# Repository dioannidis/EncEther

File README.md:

# EncEther

( version 3 )

   A single side, through hole, Arduino ethernet shield, designed in Kicad 5. 

### Main IC's

   * ENC28J60        10Base-T stand-alone ethernet controller
   * SN74HCT125N     3 state quadruple buffer for level shifting

   ( all the components datasheets can be found in the DATASHEETS directory )

### Board Info / Tips

   * As a single side board jumper wires are hard to avoid. Currently, exists 16 jumper wires, which are to be soldered first.
   * The L1 4μH inductor, is for EMC ( as per datasheet ), so you can replace it with a jumper wire.
   * The R3, R4, R11 and R12 are 49.9 Ω 1% 1/4W resistors ( as per datasheet ) but I'm using 51 Ω 1% 1/4W with success. The 49.9 Ω 1% ones are hard to find ( at least I can't find them easily ).
   * Because some jumper wires are routed under the sockets, use precision sockets which have more room under them.
   * The MagJack I use is the LMJTAB881243ML from AMPHENOL. You can find it at [TME](https://www.tme.eu/en/details/lmjtab881243m-l/rj-connectors/amphenol/lmjtab881243ml) or at [Grobotronics](https://grobotronics.com/rj45-ethernet-magjack-compatible.html) ( cheaper ).
   * The wakeup and clkout pins of ENC28J60 are not exposed. As this is an UNO shield, there is no need to provide clock to the MCU, it has it's own. And AFAIK, UIPEthernet doesn't implement the wakeup function.

### Board Configuration 

   * Jumper J3

      The CS/SS ( chip select / slave select ) signal can be connected to Arduino Pin 10 or Pin 9 using the J3 jumper.

         * Jumper on the 1-2 pins connects CS/SS to Arduino Pin 10. ( default )
         * Jumper on the 2-3 pins connects CS/SS to Arduino Pin 9.

      The Interrupt pin from the ENC28J60 it can be connected to Arduino Pin 9 or Pin 8 using the J3 jumper.

         * Jumper on the 3-4 pins connects the ENC28J60's interrupt pin to Arduino Pin 9.
         * Jumper on the 4-5 pins connects the ENC28J60's interrupt pin to Arduino Pin 8.

      Optionally, you can populate the U4 socket with an AT24MAC402-602 on a 8-Pin SOIC to DIP adapter ( something like [this](https://www.sparkfun.com/products/13655) or [this](https://www.adafruit.com/product/1212) ) to have a legit MAC Address and an extra 2Kbit serial EEPROM.

   * Jumper J4

      The I2C address of the AT24MAC402-602 can be selected using Jumper J3 as :
		
         * Jumper on 2-3 pins address is 0. ( default )
         * Jumper on 1-2 pins address is 1.

### Examples

( in EXAMPLES directory. Of course the examples work with any ENC28J60 board / module. )

   * EthernetRest 
	  
      Uses the  and  libraries.
	   
      Using the  you can control all digital and analog pins and / or executing custom functions or read custom variables.

### Gallery

   Those pictures are from v1. It didn't have the AT24MAC402-602 option and the CS/SS Pin selection designed yet.

   As you can see in the picture below, the AT24MAC402, is on the small red 8-Pin SOIC to DIP adapter on the breadboard.

-----

Copyright © 2020 Dimitrios Chr. Ioannidis

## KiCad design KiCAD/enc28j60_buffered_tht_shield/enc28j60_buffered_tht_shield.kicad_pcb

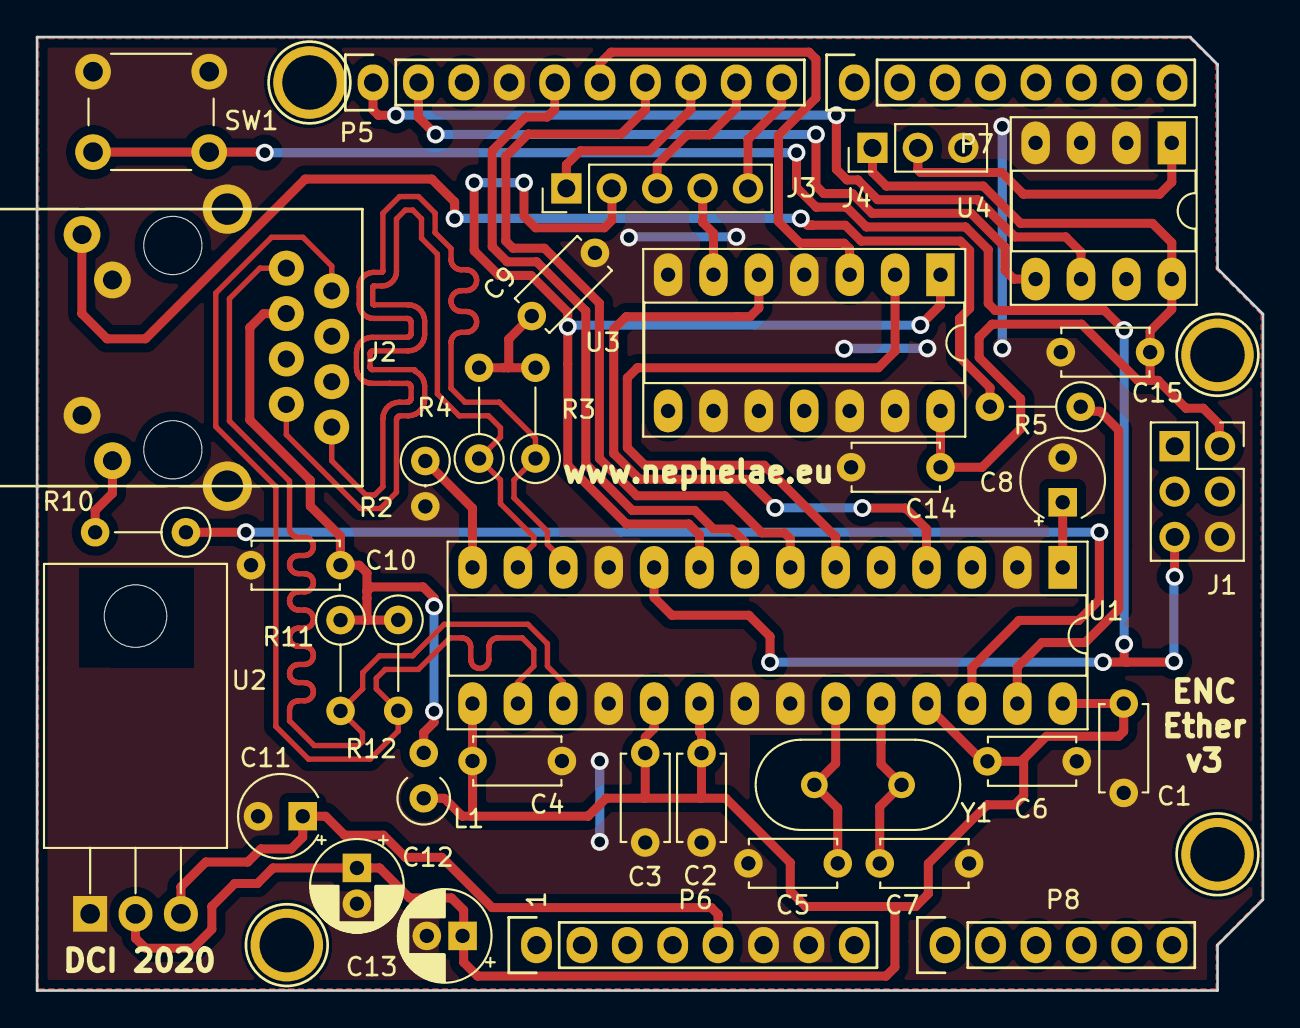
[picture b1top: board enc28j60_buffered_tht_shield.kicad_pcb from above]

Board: 2 copper layers, 68.6 x 53.3 mm, 41 parts (0 on the bottom side), 32 nets.

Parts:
C1, C2, C3, C4, C6, C9, C10, C14, C15: 100 nF; C_Disc_D4.7mm_W2.5mm_P5.00mm
C5, C7: 18 pF; C_Disc_D4.7mm_W2.5mm_P5.00mm
C8, C11: 10 μF ( Low ESR ); CP_Radial_Tantal_D4.5mm_P2.50mm
C12: 10 μF; CP_Radial_D5.0mm_P2.00mm
C13: 100 μF; CP_Radial_D5.0mm_P2.00mm
J1: AVR-ISP-6; PinSocket_2x03_P2.54mm_Vertical
J2: RJ45_MagJack_LMJTAB881X43M-L
J3: Conn_01x05_Male; PinHeader_1x05_P2.54mm_Vertical
J4: Conn_01x03_Male; PinHeader_1x03_P2.54mm_Vertical
L1: 4 μH; L_Axial_L6.6mm_D2.7mm_P2.54mm_Vertical_Vishay_IM-2
P1, P2, P3, P4: CONN_01X01; Arduino_1pin
P5: Digital; Socket_Strip_Arduino_1x10
P6: Power; Socket_Strip_Arduino_1x08
P7: Digital; Socket_Strip_Arduino_1x08
P8: Analog; Socket_Strip_Arduino_1x06
R2: 2.32 kΩ 1%; R_Axial_DIN0207_L6.3mm_D2.5mm_P2.54mm_Vertical
R3, R4, R11, R12: 49.9 Ω 1%; R_Axial_DIN0207_L6.3mm_D2.5mm_P5.08mm_Vertical
R5, R10: 180 Ω; R_Axial_DIN0207_L6.3mm_D2.5mm_P5.08mm_Vertical
SW1: SW_Push; SW_PUSH_6mm_H5mm
U1: ENC28J60x-SP; DIP-28_W7.62mm_Socket_LongPads
U2: LM1117-3.3; TO-220-3_Horizontal_TabDown
U3: 74HCT125N; DIP-14_W7.62mm_Socket_LongPads
U4: AT24MAC402-SSHM; DIP-8_W7.62mm_Socket_LongPads
Y1: 25 MHz; Crystal_HC49-4H_Vertical

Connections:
+3V3: C1.1, C2.2, C3.2, C4.2, C6.2, C12.1, C13.1, L1.1, U1.15, U1.19, U1.20, U1.25, U1.28, U2.2
+5V: C11.1, P6.5, U2.3
/8: J3.5, P5.10
/9(**): J3.3, P5.9
/10(**/SS): J3.1, P5.8
/11(**/MOSI): P5.7, U1.7
/12(MISO): P5.6, U3.3
/13(SCK): P5.5, U1.8
/A4(SDA): P5.2, U4.5
/A5(SCL): P5.1, U4.6
/A_A0: J4.2, U4.1
/INT_ENC: U1.4, U3.5
/INT_PIN: J3.4, U3.6
/LEDA: R5.1, U1.27
/LEDB: R10.1, U1.26
/MISO_ENC: U1.6, U3.2
/Reset: J1.5, SW1.2, U1.10
/SS_PIN: J3.2, U1.9, U3.1
/TPIN+: J2.7, R4.1, U1.13
/TPIN-: J2.8, R3.1, U1.12
/TPOUT+: J2.1, R11.2, U1.17
/TPOUT-: J2.2, R12.2, U1.16
GND: C1.2, C2.1, C3.1, C4.1, C5.2, C6.1, C7.2, C8.2, C9.1, C10.1, C11.2, C12.2, C13.2, C14.2, C15.2, J1.6, J2.10, J2.11, J2.M1, J2.M2, J4.3, P5.4, P6.6, P6.7, R2.2, SW1.1, U1.2, U1.11, U1.18, U1.21, U1.22, U2.1, U3.4, U3.7, U3.9, U3.10, U3.12, U3.13, U4.2, U4.3, U4.4
unnamed: C5.1, U1.23, Y1.1
unnamed: C7.1, U1.24, Y1.2
unnamed: C8.1, U1.1
unnamed: C9.2, R3.2, R4.2
unnamed: C10.2, J2.3, L1.2, R11.1, R12.1
unnamed: J2.9, R5.2
unnamed: J2.12, R10.2
unnamed: R2.1, U1.14
VCC: C14.1, C15.1, J1.2, J4.1, U3.14, U4.8

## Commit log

2020-09-03 Revision 1. 74HCT125N LM1117 3.3 ENC28J60
2020-09-12 Fixed AVR-ISP-PINS
2020-09-13 Added LM117 DataSheet
2020-09-13 Added Project Library file.
2020-09-13 Added Socket Arduino 3D Paths for preview.
2020-09-13 Add 3D images.
2020-09-14 Added AT24MAC402-602 as an option.
2020-09-14 Images and misc.
2020-09-14 Final ( ? ) v2
2020-09-14 Some changes to ground plane.
2020-09-15 Update 'README.md'
2020-09-15 Added pictures of the v1 home made prototype.
2020-09-15 Initial commit.
2020-09-15 Added an example using the UIPEthernet and aRest libraries.
2020-09-20 Fix ethernet differential pair length, skew. Fix LMJTAB881X43M Ground Pin. Added jumper for I2C address selection.
2020-09-20 Τrying to impedance to 50 Ω
2020-09-20 Fix formating
2020-09-20 Fix library problem.
